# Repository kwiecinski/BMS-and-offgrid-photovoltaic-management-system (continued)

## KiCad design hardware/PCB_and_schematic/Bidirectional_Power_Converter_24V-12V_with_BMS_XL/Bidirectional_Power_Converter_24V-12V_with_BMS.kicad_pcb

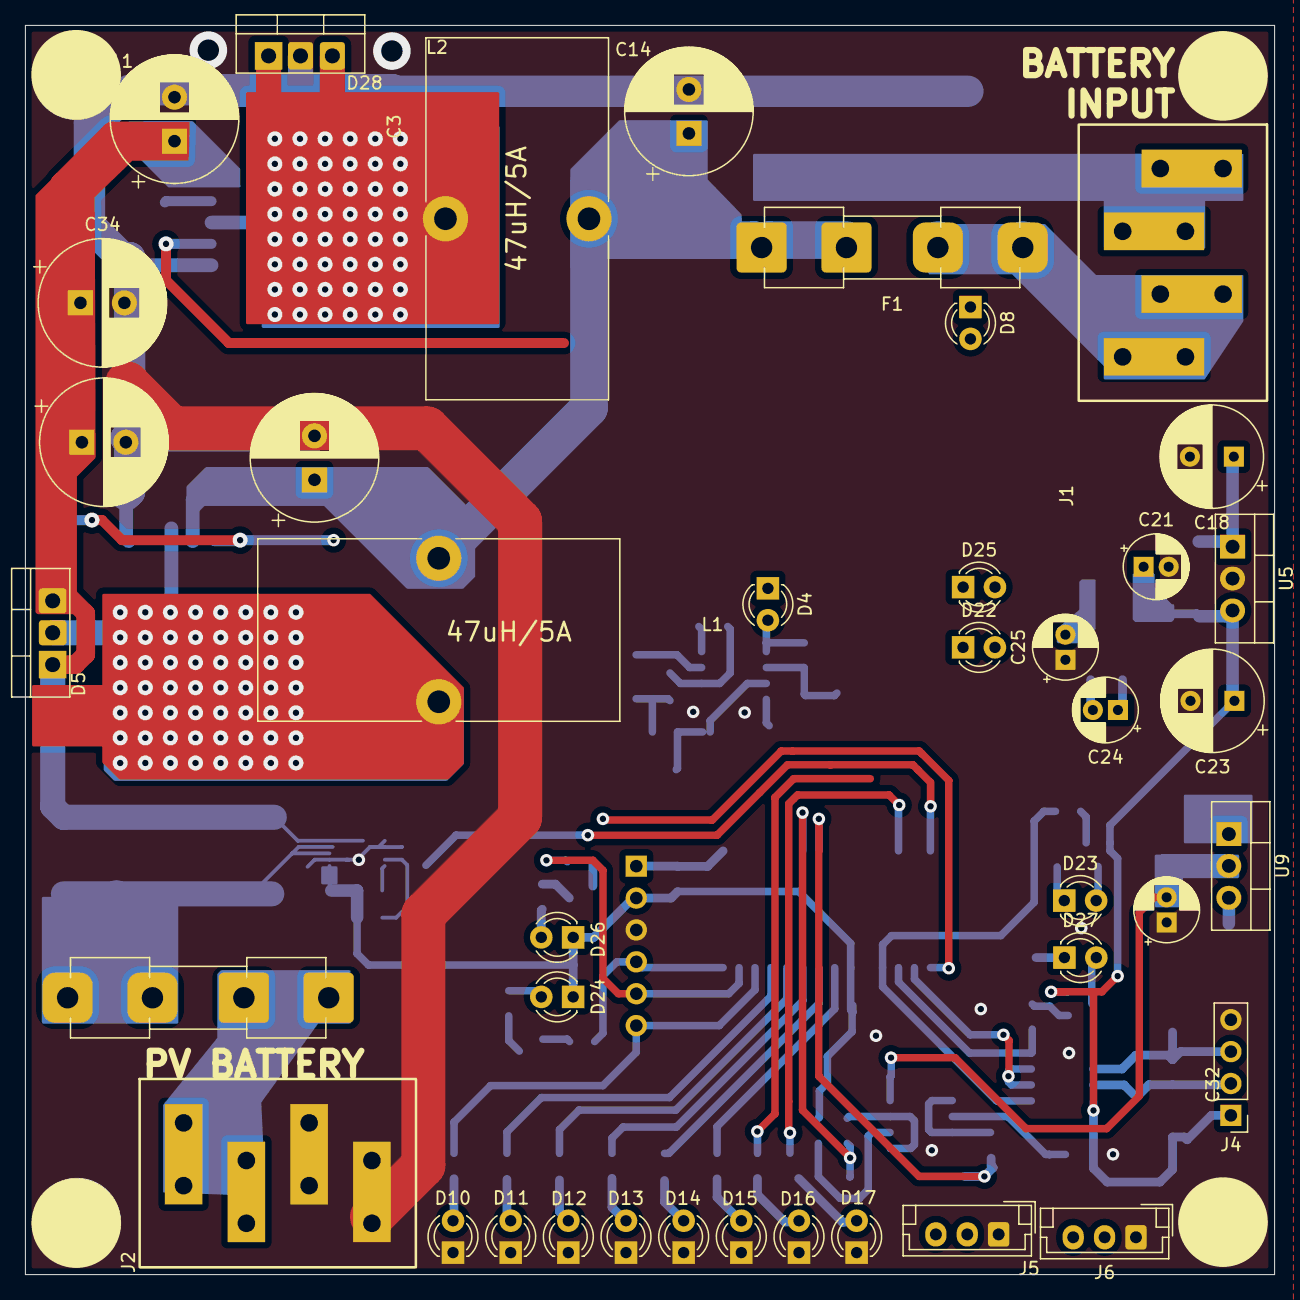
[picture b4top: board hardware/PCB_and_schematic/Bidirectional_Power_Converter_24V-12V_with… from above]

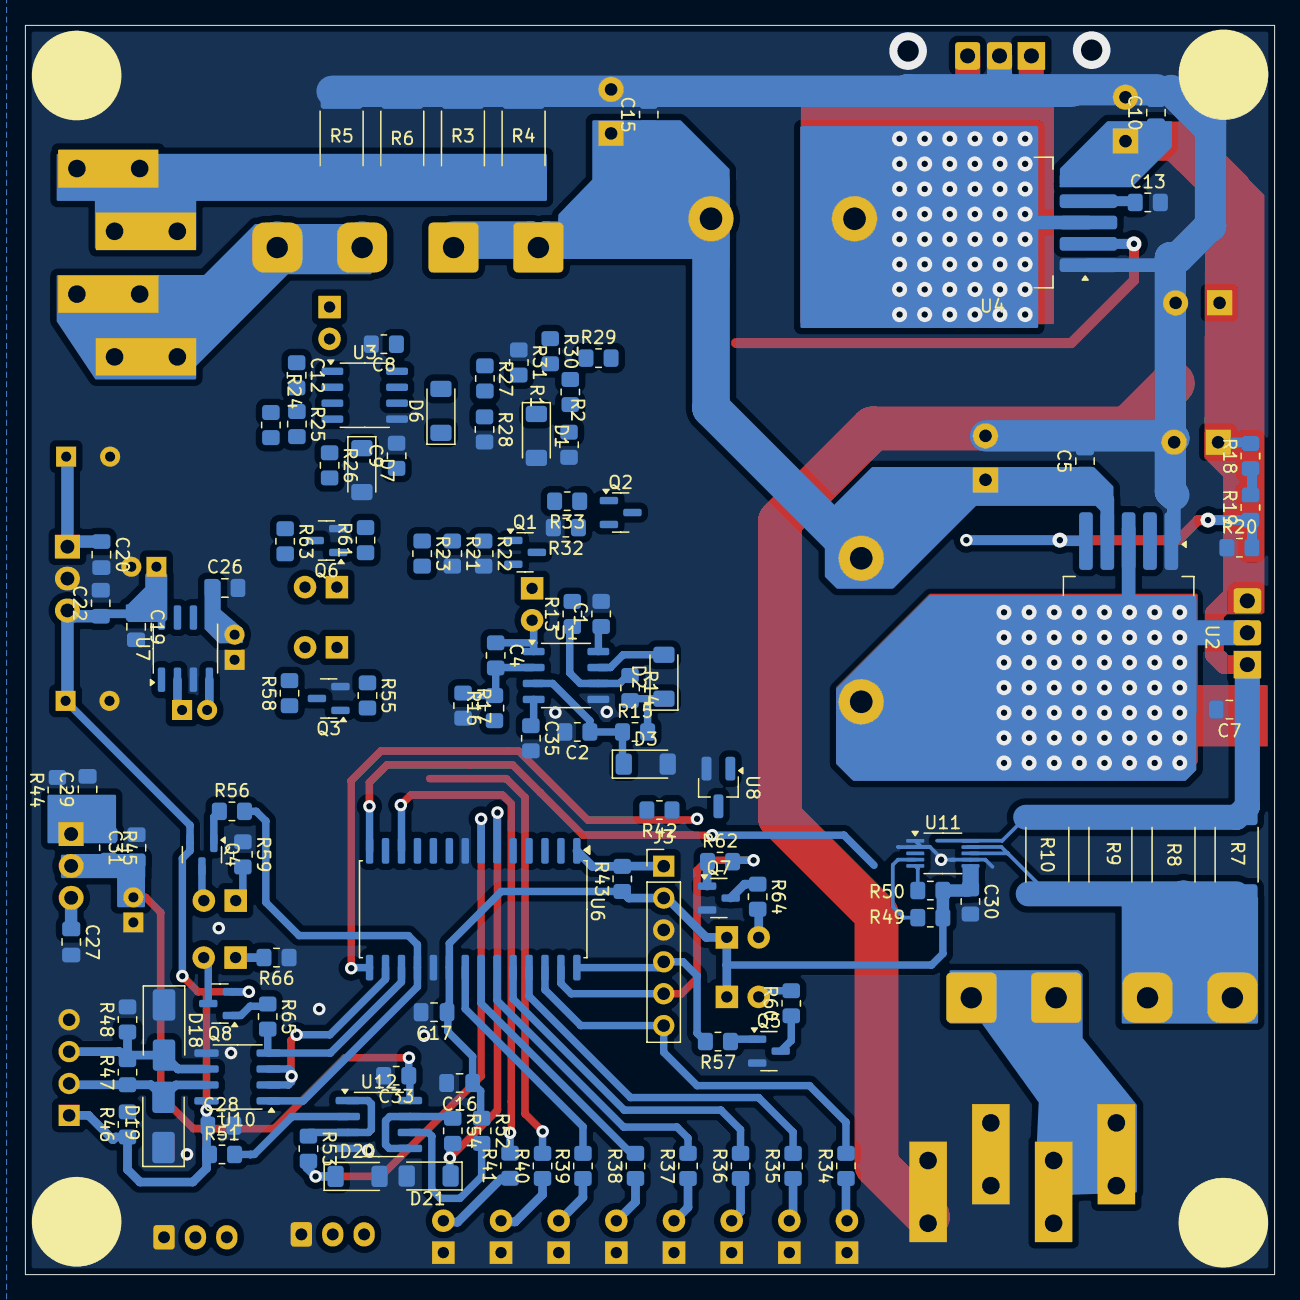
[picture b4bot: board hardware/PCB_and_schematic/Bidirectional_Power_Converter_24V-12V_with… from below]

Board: 2 copper layers, 99.5 x 99.5 mm, 156 parts (116 on the bottom side), 88 nets.

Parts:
C1, C2, C8, C9, C13, C30, C33, C35: 100n; R_0805_2012Metric_Pad1.20x1.40mm_HandSolder
C3, C6, C11, C14, C34: 1000u/35V; CP_Radial_D10.0mm_P3.50mm
C4, C12: 10n; R_0805_2012Metric_Pad1.20x1.40mm_HandSolder
C5, C7, C10, C15, C17, C19, C20, C22, C26, C27, C28, C29, C31: 100n; C_0805_2012Metric_Pad1.18x1.45mm_HandSolder
C16: 1u; C_0805_2012Metric_Pad1.18x1.45mm_HandSolder
C18: 470u/35V; CP_Radial_D8.0mm_P3.50mm
C21, C25: 22u/6,3V; CP_Radial_D5.0mm_P2.00mm
C23: 100u/10V; CP_Radial_D8.0mm_P3.50mm
C24: 10u/10V; CP_Radial_D5.0mm_P2.00mm
C32: 47u/16V; CP_Radial_D5.0mm_P2.00mm
D1, D3, D7, D20, D21: 3V3; D_MiniMELF
D2, D6: LL4148; D_MiniMELF
D4, D8, D10, D11, D12, D13, D14, D15, D16, D17, D22, D23, D24, D25, D26, D27: LED; LED_D3.0mm
D5, D28: D_Schottky_Dual; TO-220-3_Vertical-little-bigger pads
D18, D19: D_TVS; D_SMA
F1, F2: Fuse; Fuseholder_Clip-5x20mm_Eaton_1A5601-01_Inline_P20.80x6.76mm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
J1: V_IN; Flat-6,3mm-connector-4P
J2: V_OUT; Flat-6,3mm-connector-4P
J3: ICP; PinHeader_1x06_P2.54mm_Vertical
J4: RS485; PinHeader_1x04_P2.54mm_Vertical
J5: TEMP_BATT; JST_EH_B3B-EH-A_1x03_P2.50mm_Vertical
J6: TEMP_BUCK; JST_EH_B3B-EH-A_1x03_P2.50mm_Vertical
L1, L2: 47u; L_Toroid_Vertical_L28.6mm_W14.3mm_P11.43mm_Bourns_5700
Q1, Q2, Q4, Q8: BC807; SOT-23
Q3, Q5, Q6, Q7: BC817; SOT-23
R1, R43, R49, R50: 10k; R_0805_2012Metric_Pad1.20x1.40mm_HandSolder
R2: R; R_0805_2012Metric_Pad1.20x1.40mm_HandSolder
R3: 50mR; R_2512_6332Metric_Pad1.40x3.35mm_HandSolder
R4, R5, R6: 50m; R_2512_6332Metric_Pad1.40x3.35mm_HandSolder
R7, R10: 100mR; R_2512_6332Metric_Pad1.40x3.35mm_HandSolder
R8, R9: R; R_2512_6332Metric_Pad1.40x3.35mm_HandSolder
R13, R15, R16, R23, R24, R26, R27, R33, R42, R53, R54: 1k; R_0805_2012Metric_Pad1.20x1.40mm_HandSolder
R14, R25: 39k; R_0805_2012Metric_Pad1.20x1.40mm_HandSolder
R17, R28: 100k; R_0805_2012Metric_Pad1.20x1.40mm_HandSolder
R18, R29: 2,7k; R_0805_2012Metric_Pad1.20x1.40mm_HandSolder
R19, R30: 0R; R_0805_2012Metric_Pad1.20x1.40mm_HandSolder
R20, R31, R45: 240R; R_0805_2012Metric_Pad1.20x1.40mm_HandSolder
R21: 1K; R_0805_2012Metric_Pad1.20x1.40mm_HandSolder
R22, R32: 47k; R_0805_2012Metric_Pad1.20x1.40mm_HandSolder
R34, R35, R36, R37, R38, R39, R40, R41, R47: 120R; R_0805_2012Metric_Pad1.20x1.40mm_HandSolder
R44: 1k6; R_0805_2012Metric_Pad1.20x1.40mm_HandSolder
R46, R48: 510R; R_0805_2012Metric_Pad1.20x1.40mm_HandSolder
R51, R52: 150k; R_0805_2012Metric_Pad1.20x1.40mm_HandSolder
R55, R56, R57, R61, R62, R65: 10K; R_0805_2012Metric_Pad1.20x1.40mm_HandSolder
R58, R59, R60, R63, R64, R66: 220R; R_0805_2012Metric_Pad1.20x1.40mm_HandSolder
U1, U3: LM358; SO-8_3.9x4.9mm_P1.27mm
U2: XL6019; TO-263-5_TabPin3
U4: XL4015; TO-263-5_TabPin3
U5: LM7805_TO220; TO-220-3_Vertical
U6: PIC16F886-IP; SOIC-28W_7.5x17.9mm_P1.27mm
U7: ICL7660; SOIC-8_3.9x4.9mm_P1.27mm
U8: TL431LP; SOT-23_Handsoldering
U9: LM317_TO-220; TO-220-3_Vertical
U10: ST485; SOIC-8_3.9x4.9mm_P1.27mm
U11: INA226; VSSOP-10_3x3mm_P0.5mm
U12: LM358; SOIC-8_3.9x4.9mm_P1.27mm

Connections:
+5V: C16.1, C17.1, C19.1, C21.1, C22.1, C23.1, C28.1, C30.1, D22.1 (K), D24.1 (K), D25.1 (K), D26.1 (K), J3.2, J4.1, Q1.2 (E), Q2.2 (E), Q4.2 (E), Q8.2 (E), R42.2, R43.1, R46.1, R49.1, R50.1, R51.1, R52.1, U5.3 (VO), U6.20 (VDD), U7.8 (V+), U10.8 (VCC), U11.6 (VS)
+10V: C1.1, C8.1, C31.1, C32.2, C33.1, R45.2, U1.8 (V+), U3.8 (V+), U9.2 (VO), U12.8 (V+)
-5V: C25.2, C26.1, C35.1, U1.4 (V-), U3.4 (V-), U7.5 (VOUT)
/Bidirectional Power Supply/Microcontroller/RS485_A: D18.2 (A2), J4.3, R47.2, R48.1, U10.6 (A)
/Bidirectional Power Supply/Microcontroller/RS485_B: D19.2 (A2), J4.2, R46.2, R47.1, U10.7 (B)
BATT_CURRENT_SHUNT_FB: J1.1, J1.2, R3.1, R4.1, R5.1, R6.1, R13.2, R24.2
BATT_VOLTAGE_FB: D1.1 (K), R1.1, R2.2, U6.2 (ULPWU/C12IN0-/AN0/RA0)
BATT_VOLTAGE_POSITIVE: C3.1, C5.1, C14.1, C15.1, C18.1, C20.1, C27.1, F1.2, L1.1, L2.2, R1.2, R29.2, U2.4 (VIN), U5.1 (VI), U9.3 (VI)
BUCK_CURRENT_FB: C2.1, C9.1, D3.1 (K), D7.1 (K), R15.1, R26.1, U1.3 (+), U3.3 (+), U6.4 (CVref/C2IN1+/Vref-/AN2/RA2)
CLOCK: R50.2, U6.14 (RC3/SCK/SCL), U11.5 (SCL)
DBG_LED_6: J3.6, R34.2, U6.26 (~T1G/AN13/RB5)
ENABLE_BOOST: R55.2, U6.9 (CLKIN/OSC1/RA7)
ENABLE_BUCK: R23.2, R33.2, R61.2, U6.10 (CLKOUT/OSC2/RA6)
GND: C1.2, C2.2, C3.2, C5.2, C6.2, C7.2, C8.2, C9.2, C10.2, C11.2, C13.2, C14.2, C15.2, C16.2, C17.2, C18.2, C19.2, C20.2, C21.2, C22.2, C23.2, C25.1, C26.2, C27.2, C28.2, C29.2, C30.2, C31.2, C32.1, C33.2, C34.2, C35.2, D1.2 (A), D3.2 (A), D7.2 (A), D10.1 (K), D11.1 (K), D12.1 (K), D13.1 (K), D14.1 (K), D15.1 (K), D16.1 (K), D17.1 (K), D18.1 (A1), D19.1 (A1), D20.2 (A), D21.2 (A), D28.2 (A), J2.3, J2.4, J3.3, J4.4, J5.1, J6.1, Q3.2 (E), Q5.2 (E), Q6.2 (E), Q7.2 (E), R2.1, R3.2, R4.2, R5.2, R6.2, R17.2, R20.1, R21.2, R22.2, R28.2, R31.1, R32.2, R44.2, R48.2, R59.1, R66.1, U1.5 (+), U2.1 (GND), U3.5 (+), U4.1 (GND), U5.2 (GND), U6.8 (VSS), U6.19 (VSS), U7.3 (GND), U8.2 (A), U10.5 (GND), U11.1 (A1), U11.2 (A0), U11.7 (GND), U12.4 (V-)
LED_1: R39.2, U6.21 (INT/AN12/RB0)
LED_2: R38.2, U6.22 (P1C/AN10/RB1)
LED_3: R37.2, U6.23 (P1B/AN8/RB2)
LED_4: R36.2, U6.24 (PGM/C12IN2-/AN8/RB3)
LED_5: R35.2, U6.25 (P1D/AN11/RB4)
LED_7: R40.2, U6.11 (RC0/T1OSO/T1CK1)
LED_8: R41.2, U6.12 (RC1/T1OSI/CCP2)
unnamed: D2.2 (A), U1.7
unnamed: D2.1 (K), R14.2, R15.2
unnamed: C4.1, D4.2 (A), U1.1
unnamed: D4.1 (K), R19.1, R20.2, U2.5 (FB)
unnamed: D5.2 (A), L1.2, U2.3 (SW)
unnamed: D6.2 (A), U3.7
unnamed: D6.1 (K), R25.2, R26.2
unnamed: C12.1, D8.2 (A), U3.1
unnamed: D8.1 (K), Q2.3 (C), R30.1, R31.2, U4.2 (FB)
unnamed: D10.2 (A), R34.1
unnamed: D11.2 (A), R35.1
unnamed: D12.2 (A), R36.1
unnamed: D13.2 (A), R37.1
unnamed: D14.2 (A), R38.1
unnamed: D15.2 (A), R39.1
unnamed: D16.2 (A), R40.1
unnamed: D17.2 (A), R41.1
unnamed: D22.2 (A), R58.2
unnamed: D23.2 (A), Q4.3 (C)
unnamed: D23.1 (K), R59.2
unnamed: D24.2 (A), R60.2
unnamed: D25.2 (A), R63.2
unnamed: D26.2 (A), R64.2
unnamed: D27.2 (A), Q8.3 (C)
unnamed: D27.1 (K), R66.2
unnamed: F1.1, J1.3, J1.4
unnamed: F2.2, J2.1, J2.2
unnamed: J5.3, R52.2, U12.6 (-)
unnamed: J6.3, R51.2, U12.2 (-)
unnamed: Q1.1 (B), R22.1, R23.1
unnamed: Q1.3 (C), R21.1, U2.2 (EN)
unnamed: Q2.1 (B), R32.1, R33.1
unnamed: Q3.1 (B), R55.1
unnamed: Q3.3 (C), R58.1
unnamed: Q4.1 (B), R56.1
unnamed: Q5.1 (B), R57.1
unnamed: Q5.3 (C), R60.1
unnamed: Q6.1 (B), R61.1
unnamed: Q6.3 (C), R63.1
unnamed: Q7.1 (B), R62.1
unnamed: Q7.3 (C), R64.1
unnamed: Q8.1 (B), R65.1
unnamed: R18.1, R19.2
unnamed: R29.1, R30.2
unnamed: C4.2, R16.2, R17.1, U1.2 (-)
unnamed: R13.1, R14.1, U1.6 (-)
unnamed: C12.2, R27.2, R28.1, U3.2 (-)
unnamed: R24.1, R25.1, U3.6 (-)
unnamed: D28.1 (K), D28.3 (K), L2.1, U4.3 (SW)
unnamed: C13.1, U4.4 (VC)
unnamed: C24.1, U7.2 (CAP+)
unnamed: C24.2, U7.4 (CAP-)
unnamed: C29.1, R44.1, R45.1, U9.1 (ADJ)
unnamed: R53.1, U12.1, U12.3 (+)
unnamed: R54.1, U12.5 (+), U12.7
PGC_LED_STATUS_1: J3.5, R62.2, U6.27 (ICSPCLK/RB6)
PGD_LED_STATUS_2: J3.4, R57.2, U6.28 (ICSPDAT/RB7)
PV_CURRENT_SHUNT_FB: F2.1, R7.2, R8.2, R9.2, R10.2, U11.8 (Vbus), U11.9 (Vin-)
PV_VOLTAGE_POSITIVE: C6.1, C7.1, C10.1, C11.1, C34.1, D5.1 (K), D5.3 (K), R7.1, R8.1, R9.1, R10.1, R18.2, U4.5 (VIN), U11.10 (Vin+)
RS232_RX: R56.2, U6.18 (RC7/RX/DT), U10.1 (RO)
RS232_TX: R65.2, U6.17 (RC6/TX/CK), U10.4 (DI)
RS485_OUTPUT_ENABLE: U6.16 (RC5/SDO), U10.2 (~RE), U10.3 (DE)
RST: J3.1, R43.2, U6.1 (RE3/~MCLR/Vpp)
SDA: R49.2, U6.15 (RC4/SDI/SDA), U11.4 (SDA)
TEMP_BATT: D21.1 (K), R54.2, U6.6 (T0CKI/C1OUT/RA4)
TEMP_HEATSINK: D20.1 (K), R53.2, U6.7 (~SS/C2OUT/AN4/RA5)
VREF_2.5V: R16.1, R27.1, R42.1, U6.5 (C1IN+/Vref+/AN3/RA3), U8.1 (REF), U8.3 (K)

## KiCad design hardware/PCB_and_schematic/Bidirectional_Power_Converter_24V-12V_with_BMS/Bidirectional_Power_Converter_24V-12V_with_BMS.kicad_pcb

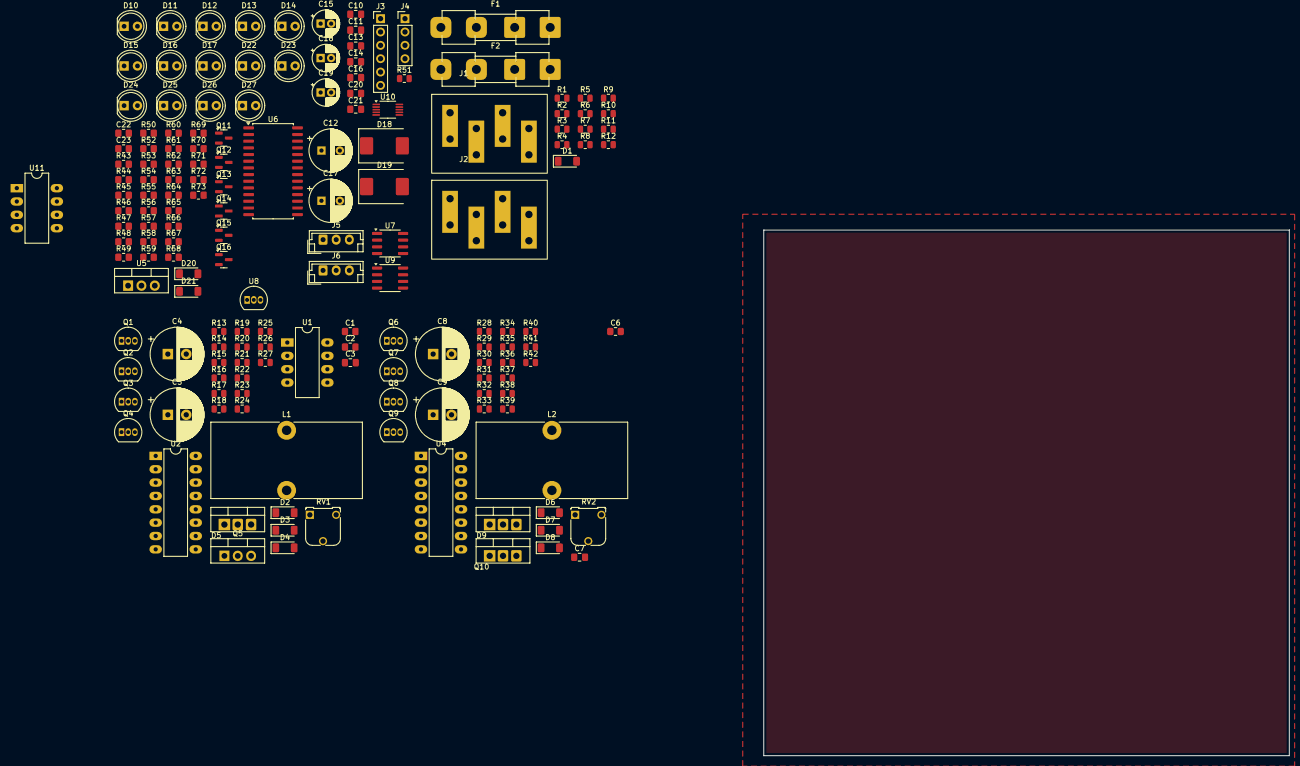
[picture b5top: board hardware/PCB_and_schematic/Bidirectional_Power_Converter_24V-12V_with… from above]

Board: 2 copper layers, 100.0 x 100.0 mm, 161 parts (0 on the bottom side), 103 nets, no tracks yet.

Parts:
C1, C2, C6, C22, C23: 100n; R_0805_2012Metric_Pad1.20x1.40mm_HandSolder
C3: 1n; C_0805_2012Metric_Pad1.18x1.45mm_HandSolder
C4, C5, C8, C9: 1000u/35V; CP_Radial_D10.0mm_P3.50mm
C7: 2.2n; C_0805_2012Metric_Pad1.18x1.45mm_HandSolder
C10: 1u; C_0805_2012Metric_Pad1.18x1.45mm_HandSolder
C11, C13, C14, C16, C20, C21: 100n; C_0805_2012Metric_Pad1.18x1.45mm_HandSolder
C12: 470u/35V; CP_Radial_D8.0mm_P3.50mm
C15, C19: 22u/6,3V; CP_Radial_D5.0mm_P2.00mm
C17: 100u/10V; CP_Radial_D8.0mm_P3.50mm
C18: 10u/10V; CP_Radial_D5.0mm_P2.00mm
D1, D2, D6, D20, D21: 3V3; D_MiniMELF
D3, D7: D_Schottky; D_MiniMELF
D4, D8: LL4148; D_MiniMELF
D5, D9: D_Schottky_Dua; TO-220-3_Vertical-little-bigger pads
D10, D11, D12, D13, D14, D15, D16, D17, D22, D23, D24, D25, D26, D27: LED; LED_D5.0mm
D18, D19: D_TVS; D_SMC
F1, F2: Fuse; Fuseholder_Clip-5x20mm_Eaton_1A5601-01_Inline_P20.80x6.76mm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
J1: V_IN; Flat-6,3mm-connector-4P
J2: V_OUT; Flat-6,3mm-connector-4P
J3: ICP; PinHeader_1x06_P2.54mm_Vertical
J4: RS485; PinHeader_1x04_P2.54mm_Vertical
J5: TEMP_BATT; JST_EH_B3B-EH-A_1x03_P2.50mm_Vertical
J6: TEMP_BUCK; JST_EH_B3B-EH-A_1x03_P2.50mm_Vertical
L1: 60uH (100kHz); L_Toroid_Vertical_L28.6mm_W14.3mm_P11.43mm_Bourns_5700
L2: L; L_Toroid_Vertical_L28.6mm_W14.3mm_P11.43mm_Bourns_5700
Q1, Q2, Q3, Q6, Q7, Q8: BC337; TO-92_Inline
Q4, Q9: BC327; TO-92_Inline
Q5: IRF540N; TO-220-3_Vertical
Q10: PMOS; TO-220-3_Vertical-little-bigger pads
Q11, Q13, Q14, Q15: BC817; SOT-23
Q12, Q16: BC807; SOT-23
R1, R17, R19, R25, R32, R33, R40: 10k; R_0805_2012Metric
R2, R4, R5, R8, R9, R11, R12, R13, R14, R23, R27, R28, R31, R36, R38, R42: R; R_0805_2012Metric
R3, R6, R7, R10: 100mR; R_0805_2012Metric
R15, R29: 6k8; R_0805_2012Metric
R16, R30: 4k7; R_0805_2012Metric
R18, R26, R35, R41, R51: 1k; R_0805_2012Metric
R20, R34: 470R; R_0805_2012Metric
R21: 4.7k; R_0805_2012Metric
R22, R37: 47k; R_0805_2012Metric
R24, R39: 0R; R_0805_2012Metric
R43, R44, R45, R46, R47, R48, R49, R50, R54: 120R; R_0805_2012Metric_Pad1.20x1.40mm_HandSolder
R52, R56, R57: 10k; R_0805_2012Metric_Pad1.20x1.40mm_HandSolder
R53, R55: 510R; R_0805_2012Metric_Pad1.20x1.40mm_HandSolder
R58, R59: 150k; R_0805_2012Metric_Pad1.20x1.40mm_HandSolder
R60, R61: 1k; R_0805_2012Metric_Pad1.20x1.40mm_HandSolder
R62, R63, R64, R68, R69, R72: 10K; R_0805_2012Metric_Pad1.20x1.40mm_HandSolder
R65, R66, R67, R70, R71, R73: 220R; R_0805_2012Metric_Pad1.20x1.40mm_HandSolder
RV1, RV2: 10K; Potentiometer_Runtron_RM-065_Vertical
U1, U11: LM358; CERDIP-8_W7.62mm_SideBrazed_LongPads
U2, U4: TL494; CERDIP-16_W7.62mm_SideBrazed_LongPads
U5: LM7805_TO220; TO-220-3_Vertical
U6: PIC16F886-IP; SOIC-28W_7.5x17.9mm_P1.27mm
U7: ICL7660; SOIC-8_3.9x4.9mm_P1.27mm
U8: TL431LP; TO-92_Inline
U9: ST485; SOIC-8_3.9x4.9mm_P1.27mm
U10: INA226; VSSOP-10_3x3mm_P0.5mm

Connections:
+5V: C1.1, C10.1, C11.1, C13.1, C15.1, C16.1, C17.1, C21.1, C22.1, C23.1, D22.1 (K), D24.1 (K), D25.1 (K), D26.1 (K), J3.2, J4.1, Q12.2 (E), Q16.2 (E), R51.2, R52.1, R53.1, R56.1, R57.1, R58.1, R59.1, U5.3 (VO), U6.20 (VDD), U7.8 (V+), U9.8 (VCC), U10.6 (VS), U11.8 (V+)
-5V: C19.2, C20.1, U1.4 (V-), U7.5 (VOUT)
/Bidirectional Power Supply/Boost Converter/VREF_2V: R15.2, R16.1, R20.1
/Bidirectional Power Supply/Boost Converter/VREF_5V: R15.1, R19.1, U2.14 (REF)
/Bidirectional Power Supply/Buck Converter/VREF_2V: R29.2, R30.1, R34.1
/Bidirectional Power Supply/Buck Converter/VREF_5V: R29.1, R33.1, U4.14 (REF)
/Bidirectional Power Supply/Microcontroller/RS485_A: D18.2 (A2), J4.3, R54.2, R55.1, U9.6 (A)
/Bidirectional Power Supply/Microcontroller/RS485_B: D19.2 (A2), J4.2, R53.2, R54.1, U9.7 (B)
BATT_CURRENT_SHUNT_FB: J1.1, J1.2, R3.1, R4.1, R5.1, R6.1, R13.2, R28.2
BATT_VOLTAGE_FB: D1.1 (K), R1.1, R2.2, U4.1 (1IN+), U6.2 (ULPWU/C12IN0-/AN0/RA0)
BATT_VOLTAGE_POSITIVE: C8.1, C9.1, C12.1, C14.1, F1.2, L1.1, L2.2, Q3.1 (C), R1.2, R23.1, R25.1, U2.12 (VCC), U5.1 (VI)
BOOST_CURRENT_FB: C2.1, D2.1 (K), D3.1 (K), R18.1, U2.16 (2IN+), U6.3 (C12IN1-/AN1/RA1)
BUCK_CURRENT_FB: C6.1, D6.1 (K), D7.1 (K), R35.1, U4.16 (2IN+), U6.4 (CVref/C2IN1+/Vref-/AN2/RA2)
CLOCK: R57.2, U6.14 (RC3/SCK/SCL), U10.5 (SCL)
DBG_LED_6: R45.2, U6.26 (~T1G/AN13/RB5)
ENABLE_BOOST: R17.1, R62.2, U6.25 (P1D/AN11/RB4)
ENABLE_BUCK: R32.1, R68.2, U6.24 (PGM/C12IN2-/AN8/RB3)
GND: C1.2, C2.2, C3.2, C4.2, C5.2, C6.2, C7.2, C8.2, C9.2, C10.2, C11.2, C12.2, C13.2, C14.2, C15.2, C16.2, C17.2, C19.1, C20.2, C21.2, C22.2, C23.2, D1.2 (A), D2.2 (A), D3.2 (A), D6.2 (A), D7.2 (A), D9.1 (A), D10.1 (K), D11.1 (K), D12.1 (K), D13.1 (K), D14.1 (K), D15.1 (K), D16.1 (K), D17.1 (K), D18.1 (A1), D19.1 (A1), D20.2 (A), D21.2 (A), J2.3, J2.4, J3.3, J4.4, J5.1, J6.1, Q1.3 (E), Q2.3 (E), Q4.1 (C), Q5.3 (S), Q6.3 (E), Q7.3 (E), Q9.1 (C), Q11.2 (E), Q13.2 (E), Q14.2 (E), Q15.2 (E), R2.1, R3.2, R4.2, R5.2, R6.2, R12.1, R16.2, R21.2, R30.2, R36.2, R55.2, R66.1, R73.1, U1.3 (+), U1.5 (+), U2.7 (GND), U2.9 (E1), U2.10 (E2), U2.13 (OUTCTRL), U4.7 (GND), U4.9 (E1), U4.10 (E2), U4.13 (OUTCTRL), U5.2 (GND), U6.8 (VSS), U6.19 (VSS), U7.3 (GND), U8.2 (A), U9.5 (GND), U10.1 (A1), U10.2 (A0), U10.7 (GND), U11.4 (V-)
LED_1: R50.2, U6.10 (CLKOUT/OSC2/RA6)
LED_2: R49.2, U6.9 (CLKIN/OSC1/RA7)
LED_3: R48.2, U6.21 (INT/AN12/RB0)
LED_4: R47.2, U6.22 (P1C/AN10/RB1)
LED_5: R46.2, U6.23 (P1B/AN8/RB2)
LED_7: R44.2, U6.11 (RC0/T1OSO/T1CK1)
LED_8: R43.2, U6.12 (RC1/T1OSI/CCP2)
unnamed: D4.2 (A), Q5.1 (G), R27.2
unnamed: D4.1 (K), Q3.3 (E), Q4.3 (E), R27.1
unnamed: D5.1 (A), L1.2, Q5.2 (D)
unnamed: D8.2 (A), Q10.2 (G), R42.2
unnamed: D8.1 (K), Q8.3 (E), Q9.3 (E), R42.1
unnamed: D10.2 (A), R43.1
unnamed: D11.2 (A), R44.1
unnamed: D12.2 (A), R45.1
unnamed: D13.2 (A), R46.1
unnamed: D14.2 (A), R47.1
unnamed: D15.2 (A), R48.1
unnamed: D16.2 (A), R49.1
unnamed: D17.2 (A), R50.1
unnamed: D22.2 (A), R65.2
unnamed: D23.2 (A), Q12.3 (C)
unnamed: D23.1 (K), R66.2
unnamed: D24.2 (A), R67.2
unnamed: D25.2 (A), R70.2
unnamed: D26.2 (A), R71.2
unnamed: D27.2 (A), Q16.3 (C)
unnamed: D27.1 (K), R73.2
unnamed: F1.1, J1.3, J1.4
unnamed: F2.2, J2.1, J2.2
unnamed: J5.3, R59.2, U11.6 (-)
unnamed: J6.3, R58.2, U11.2 (-)
unnamed: Q1.2 (B), R17.2
unnamed: Q1.1 (C), R19.2, U2.4 (DTC)
unnamed: Q2.2 (B), R23.2, R24.1, U2.8 (C1), U2.11 (C2)
unnamed: Q2.1 (C), R26.2
unnamed: Q3.2 (B), Q4.2 (B), R24.2, R25.2, R26.1
unnamed: Q6.2 (B), R32.2
unnamed: Q6.1 (C), R33.2, U4.4 (DTC)
unnamed: Q7.2 (B), R38.2, R39.2, U4.8 (C1), U4.11 (C2)
unnamed: Q7.1 (C), R41.2
unnamed: Q8.2 (B), Q9.2 (B), R39.1, R40.2, R41.1
unnamed: D9.2 (K), D9.3 (K), L2.1, Q10.1 (D)
unnamed: Q8.1 (C), Q10.3 (S), R38.1, R40.1, U4.12 (VCC)
unnamed: Q11.1 (B), R62.1
unnamed: Q11.3 (C), R65.1
unnamed: Q12.1 (B), R63.1
unnamed: Q13.1 (B), R64.1
unnamed: Q13.3 (C), R67.1
unnamed: Q14.1 (B), R68.1
unnamed: Q14.3 (C), R70.1
unnamed: Q15.1 (B), R69.1
unnamed: Q15.3 (C), R71.1
unnamed: Q16.1 (B), R72.1
unnamed: R14.2, R18.2, U1.1
unnamed: R21.1, RV1.1
unnamed: R31.2, R35.2, U1.7
unnamed: R36.1, RV2.1
unnamed: R13.1, R14.1, U1.2 (-)
unnamed: R28.1, R31.1, U1.6 (-)
unnamed: R20.2, R22.1, U2.2 (1IN-), U2.15 (2IN-)
unnamed: C3.1, U2.5 (CT)
unnamed: R22.2, U2.3 (FB)
unnamed: RV1.2, RV1.3, U2.6 (RT)
unnamed: R34.2, R37.1, U4.2 (1IN-), U4.15 (2IN-)
unnamed: C7.1, U4.5 (CT)
unnamed: R37.2, U4.3 (FB)
unnamed: RV2.2, RV2.3, U4.6 (RT)
unnamed: R51.1, U6.5 (C1IN+/Vref+/AN3/RA3), U8.1 (REF), U8.3 (K)
unnamed: C18.1, U7.2 (CAP+)
unnamed: C18.2, U7.4 (CAP-)
unnamed: R60.1, U11.1, U11.3 (+)
unnamed: R61.1, U11.5 (+), U11.7
PGC_LED_STATUS_1: R69.2, U6.27 (ICSPCLK/RB6)
PGD_LED_STATUS_2: R64.2, U6.28 (ICSPDAT/RB7)
PV_CURRENT_SHUNT_FB: F2.1, R7.2, R8.2, R9.2, R10.2, R11.2, U10.8 (Vbus), U10.9 (Vin-)
PV_VOLTAGE_FB: R11.1, R12.2, U2.1 (1IN+)
PV_VOLTAGE_POSITIVE: C4.1, C5.1, D5.2 (K), D5.3 (K), R7.1, R8.1, R9.1, R10.1, U10.10 (Vin+)
RS232_RX: R63.2, U6.18 (RC7/RX/DT), U9.1 (RO)
RS232_TX: R72.2, U6.17 (RC6/TX/CK), U9.4 (DI)
RS485_OUTPUT_ENABLE: U6.16 (RC5/SDO), U9.2 (~RE), U9.3 (DE)
RST: J3.1, R52.2, U6.1 (RE3/~MCLR/Vpp)
SDA: R56.2, U6.15 (RC4/SDI/SDA), U10.4 (SDA)
TEMP_BATT: D21.1 (K), R61.2, U6.6 (T0CKI/C1OUT/RA4)
TEMP_HEATSINK: D20.1 (K), R60.2, U6.7 (~SS/C2OUT/AN4/RA5)

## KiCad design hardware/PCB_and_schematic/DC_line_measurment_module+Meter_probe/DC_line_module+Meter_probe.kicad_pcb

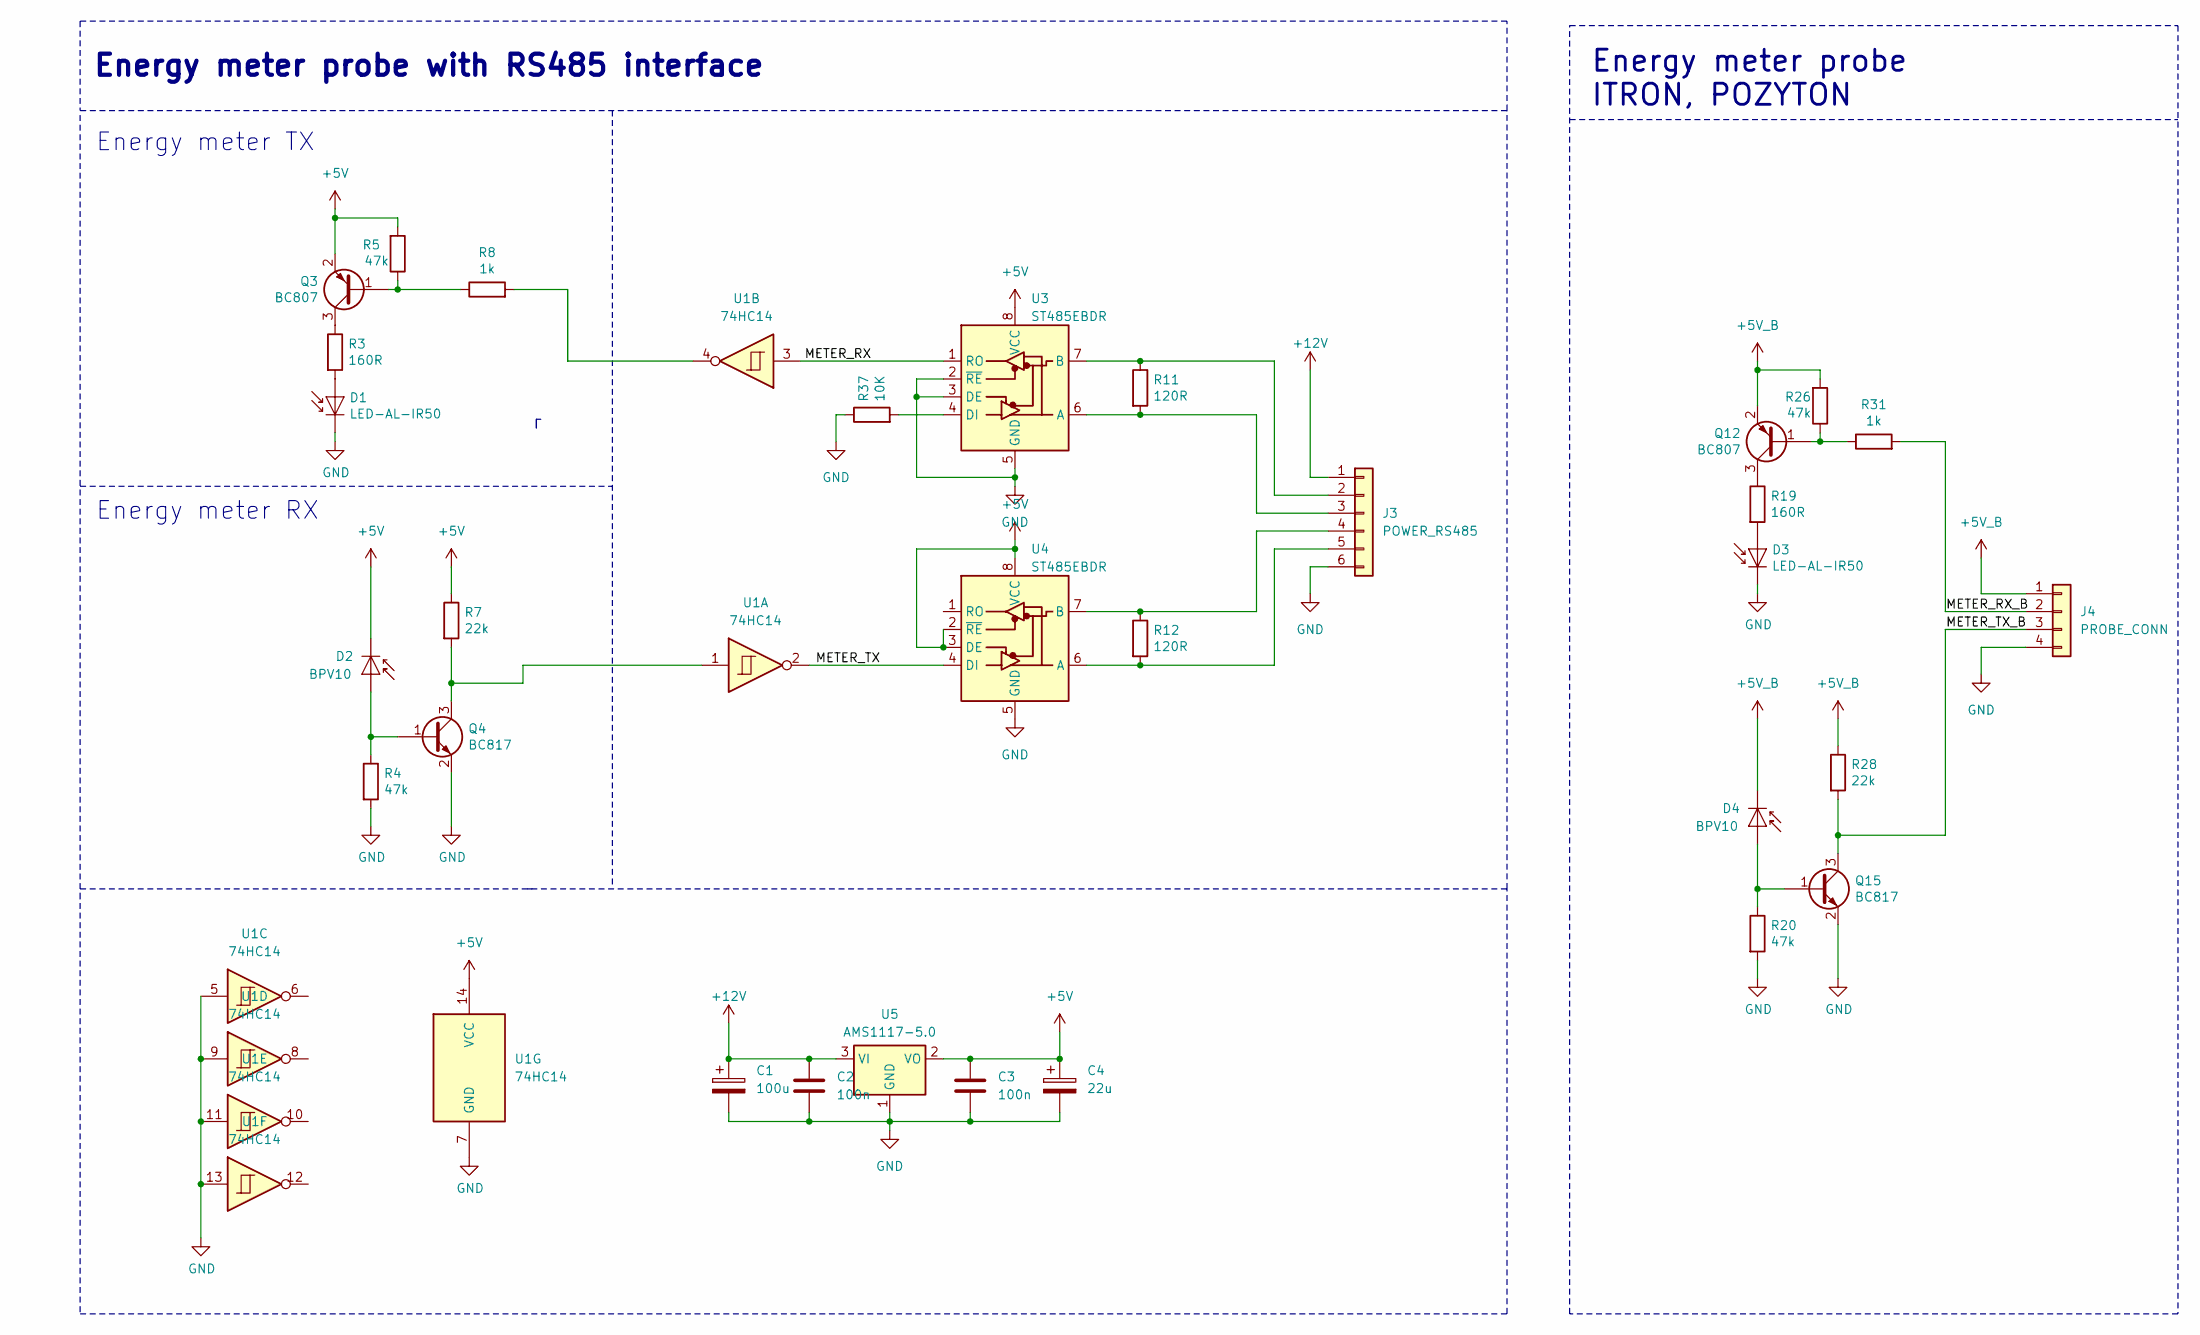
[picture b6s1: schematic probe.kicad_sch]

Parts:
C1: 100u; CP_EIA-6032-28_Kemet-C
C2, C3: 100n; C_0805_2012Metric_Pad1.18x1.45mm_HandSolder
C4: 22u; CP_EIA-3528-21_Kemet-B
D1, D3: LED-AL-IR50; LED_D5.0mm
D2, D4: BPV10; LED_D5.0mm
J3: POWER_RS485; Pin_Header_Straight_1x06_Pitch2.54mm
J4: PROBE_CONN; PinHeader_1x04_P2.54mm_Vertical
Q3, Q12: BC807; SOT-23
Q4, Q15: BC817; SOT-23
R3, R19: 160R; R_0805_2012Metric_Pad1.20x1.40mm_HandSolder
R4, R5, R20, R26: 47k; R_0805_2012Metric_Pad1.20x1.40mm_HandSolder
R7, R28: 22k; R_0805_2012Metric_Pad1.20x1.40mm_HandSolder
R8, R31: 1k; R_0805_2012Metric_Pad1.20x1.40mm_HandSolder
R11, R12: 120R; R_0805_2012Metric_Pad1.20x1.40mm_HandSolder
R37: 10K; R_0805_2012Metric_Pad1.20x1.40mm_HandSolder
U1: 74HC14; SO-16_3.9x9.9mm_P1.27mm
U3, U4: ST485EBDR; SOIC-8_3.9x4.9mm_P1.27mm
U5: AMS1117-5.0; SOT-223-3_TabPin2

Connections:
+5V: C3.1, C4.1, D2.1 (K), Q3.2 (E), R5.2, R7.1, U1.14 (VCC), U3.8 (VCC), U4.2 (~RE), U4.3 (DE), U4.8 (VCC), U5.2 (VO); also elsewhere on the board
+5V_B: D4.1 (K), J4.1, Q12.2 (E), R26.2, R28.1
+12V: C1.1, C2.1, J3.1, U5.3 (VI)
/Energy meter probe/METER_RX: U1.3, U3.1 (RO)
/Energy meter probe/METER_RX_B: J4.2, R31.2
/Energy meter probe/METER_TX: U1.2, U4.4 (DI)
/Energy meter probe/METER_TX_B: J4.3, Q15.3 (C), R28.2
GND: C1.2, C2.2, C3.2, C4.2, D1.1 (K), D3.1 (K), J3.6, J4.4, Q4.2 (E), Q15.2 (E), R4.2, R20.2, R37.1, U1.5, U1.7 (GND), U1.9, U1.11, U1.13, U3.2 (~RE), U3.3 (DE), U3.5 (GND), U4.5 (GND), U5.1 (GND); also elsewhere on the board
unnamed: D1.2 (A), R3.2
unnamed: D2.2 (A), Q4.1 (B), R4.1
unnamed: D3.2 (A), R19.2
unnamed: D4.2 (A), Q15.1 (B), R20.1
unnamed: J3.2, R11.1, U3.7 (B)
unnamed: J3.3, R11.2, U3.6 (A)
unnamed: J3.4, R12.1, U4.7 (B)
unnamed: J3.5, R12.2, U4.6 (A)
unnamed: Q3.1 (B), R5.1, R8.1
unnamed: Q3.3 (C), R3.1
unnamed: Q4.3 (C), R7.2, U1.1
unnamed: Q12.1 (B), R26.1, R31.1
unnamed: Q12.3 (C), R19.1
unnamed: R8.2, U1.4
unnamed: R37.2, U3.4 (DI)

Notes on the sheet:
Energy meter RX
Energy meter probe ITRON, POZYTON
Energy meter TX
Energy meter probe with RS485 interface
